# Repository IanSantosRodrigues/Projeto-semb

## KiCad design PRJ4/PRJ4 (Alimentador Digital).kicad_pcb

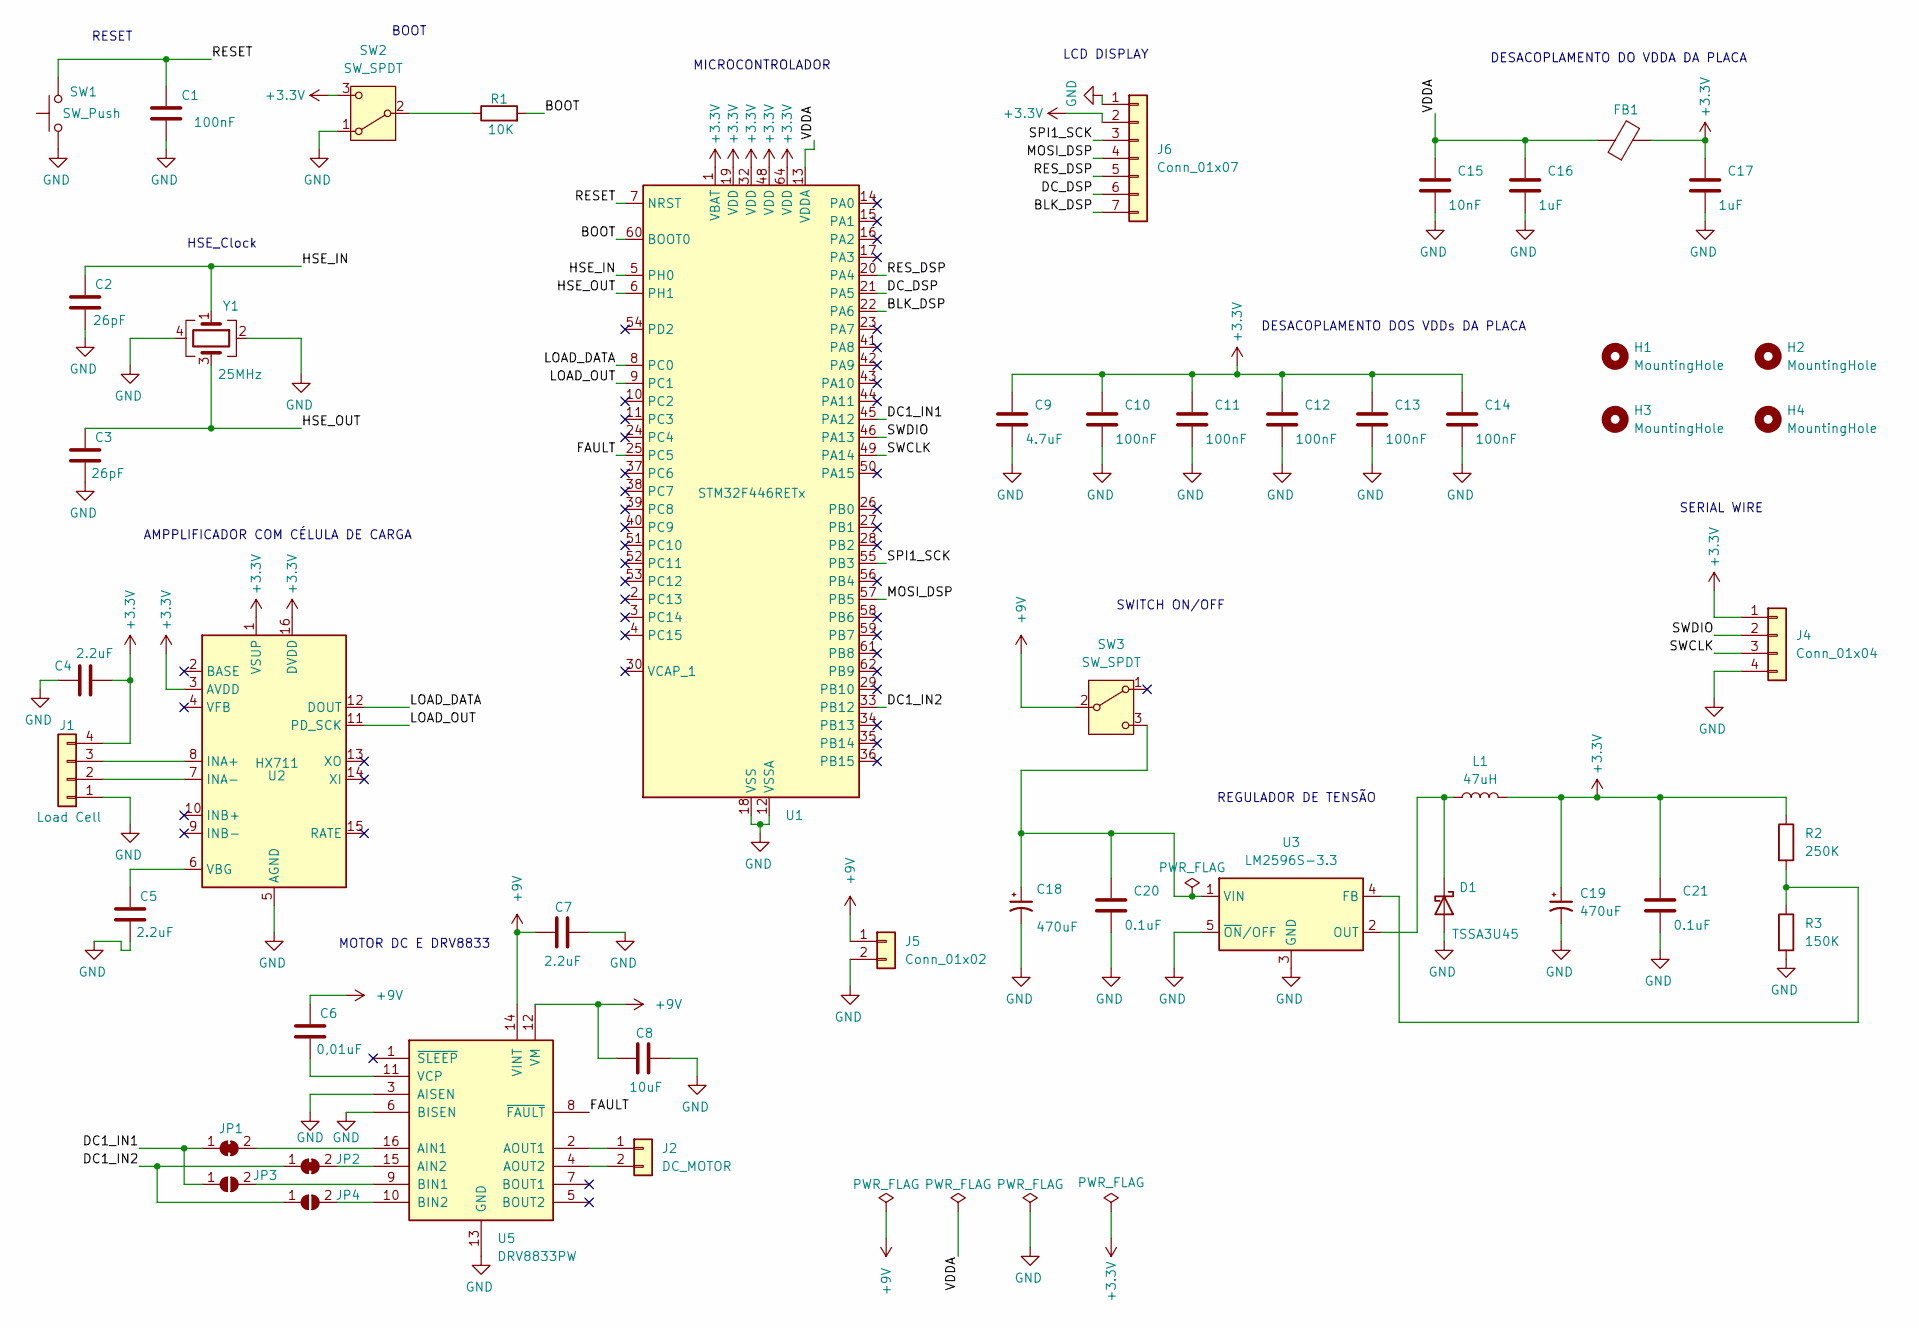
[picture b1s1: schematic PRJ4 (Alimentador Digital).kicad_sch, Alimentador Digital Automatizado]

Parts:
C1, C10, C11, C12, C13, C14: 100nF; C_0603_1608Metric
C2, C3: 26pF; C_0603_1608Metric
C4, C5, C7: 2.2uF; C_0603_1608Metric
C6: 0,01uF; C_0603_1608Metric
C8: 10uF; C_0603_1608Metric
C9: 4.7uF; C_0603_1608Metric
C15: 10nF; C_0603_1608Metric
C16, C17: 1uF; C_0603_1608Metric
C18, C19: 470uF; CP_Elec_10x12.5
C20, C21: 0.1uF; C_0603_1608Metric
D1: TSSA3U45; D_0603_1608Metric_Pad1.05x0.95mm_HandSolder
FB1: FerriteBead; L_0603_1608Metric_Pad1.05x0.95mm_HandSolder
H1, H2, H3, H4: MountingHole; MountingHole_3.2mm_M3
J1: Load Cell; PinHeader_1x04_P2.54mm_Vertical
J2: DC_MOTOR; PinHeader_1x02_P2.54mm_Vertical
J4: Conn_01x04; PinHeader_1x04_P2.54mm_Vertical
J5: Conn_01x02; PinHeader_1x02_P2.54mm_Vertical
J6: Conn_01x07; PinHeader_1x07_P2.54mm_Vertical
JP1, JP2: SolderJumper_2_Bridged; SolderJumper-2_P1.3mm_Bridged_RoundedPad1.0x1.5mm
JP3, JP4: SolderJumper_2_Open; SolderJumper-2_P1.3mm_Open_RoundedPad1.0x1.5mm
L1: 47uH; L_6.3x6.3_H3
R1: 10K; R_0603_1608Metric
R2: 250K; R_0805_2012Metric_Pad1.20x1.40mm_HandSolder
R3: 150K; R_0805_2012Metric_Pad1.20x1.40mm_HandSolder
SW1: SW_Push; SW_SPST_B3U-1000P-B
SW2, SW3: SW_SPDT; SW_SPDT_CK_JS102011SAQN
U1: STM32F446RETx; LQFP-64_10x10mm_P0.5mm
U2: HX711; SOP-16_3.9x9.9mm_P1.27mm
U3: LM2596S-3.3; TO-263-5_TabPin3
U5: DRV8833PW; TSSOP-16_4.4x5mm_P0.65mm
Y1: 25MHz; Crystal_SMD_SeikoEpson_FA238V-4Pin_3.2x2.5mm

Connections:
+3.3V: C4.2, C9.1, C10.1, C11.1, C12.1, C13.1, C14.1, C17.1, C19.1, C21.1, FB1.2, J1.4, J4.1, J6.2, L1.2, R2.1, SW2.3 (C), U1.1 (VBAT), U1.19 (VDD), U1.32 (VDD), U1.48 (VDD), U1.64 (VDD), U2.1 (VSUP), U2.3 (AVDD), U2.16 (DVDD)
+9V: C6.1, C7.1, C8.1, J5.1, SW3.2 (B), U5.12 (VM), U5.14 (VINT)
/BLK_DSP: J6.7, U1.22 (PA6)
/BOOT: R1.2, U1.60 (BOOT0)
/CLK__DSP: J6.3, U1.55 (PB3)
/DC1_IN1: JP1.1 (A), JP3.1 (A), U1.45 (PA12)
/DC1_IN2: JP2.1 (A), JP4.1 (A), U1.33 (PB12)
/DC_DSP: J6.6, U1.21 (PA5)
/FAULT: U1.25 (PC5), U5.8 (~FAULT)
/HSE_IN: C2.1, U1.5 (PH0), Y1.1
/HSE_OUT: C3.1, U1.6 (PH1), Y1.3
/LOAD_DATA: U1.8 (PC0), U2.12 (DOUT)
/LOAD_OUT: U1.9 (PC1), U2.11 (PD_SCK)
/MOSI_DSP: J6.4, U1.57 (PB5)
/RESET: C1.1, SW1.2, U1.7 (NRST)
/RES_DSP: J6.5, U1.20 (PA4)
/SWCLK: J4.3, U1.49 (PA14)
/SWDIO: J4.2, U1.46 (PA13)
/VDDA: C15.1, C16.1, FB1.1, U1.13 (VDDA)
GND: C1.2, C2.2, C3.2, C4.1, C5.2, C7.2, C8.2, C9.2, C10.2, C11.2, C12.2, C13.2, C14.2, C15.2, C16.2, C17.2, C18.2, C19.2, C20.2, C21.2, D1.2 (A), J1.1, J4.4, J5.2, J6.1, R3.2, SW1.1, SW2.1 (A), U1.12 (VSSA), U1.18 (VSS), U1.31 (VSS), U1.47 (VSS), U1.63 (VSS), U2.5 (AGND), U3.3 (GND), U3.5 (~ON/OFF), U5.3 (AISEN), U5.6 (BISEN), U5.13 (GND), Y1.2, Y1.4
unnamed: D1.1 (K), L1.1, U3.2 (OUT)
unnamed: J1.2, U2.7 (INA-)
unnamed: J1.3, U2.8 (INA+)
unnamed: J2.1, U5.2 (AOUT1)
unnamed: J2.2, U5.4 (AOUT2)
unnamed: JP1.2 (B), U5.16 (AIN1)
unnamed: JP2.2 (B), U5.15 (AIN2)
unnamed: JP3.2 (B), U5.9 (BIN1)
unnamed: JP4.2 (B), U5.10 (BIN2)
unnamed: R1.1, SW2.2 (B)
unnamed: C18.1, C20.1, SW3.3 (C), U3.1 (VIN)
unnamed: C5.1, U2.6 (VBG)
unnamed: R2.2, R3.1, U3.4 (FB)
unnamed: C6.2, U5.11 (VCP)

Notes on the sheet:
DESACOPLAMENTO DOS VDDs DA PLACA
MOTOR DC E DRV8833
RESET
DESACOPLAMENTO DO VDDA DA PLACA
REGULADOR DE TENSÃO
BOOT
HSE_Clock
LCD DISPLAY
MICROCONTROLADOR
SWITCH ON/OFF
SERIAL WIRE
AMPPLIFICADOR COM CÉLULA DE CARGA

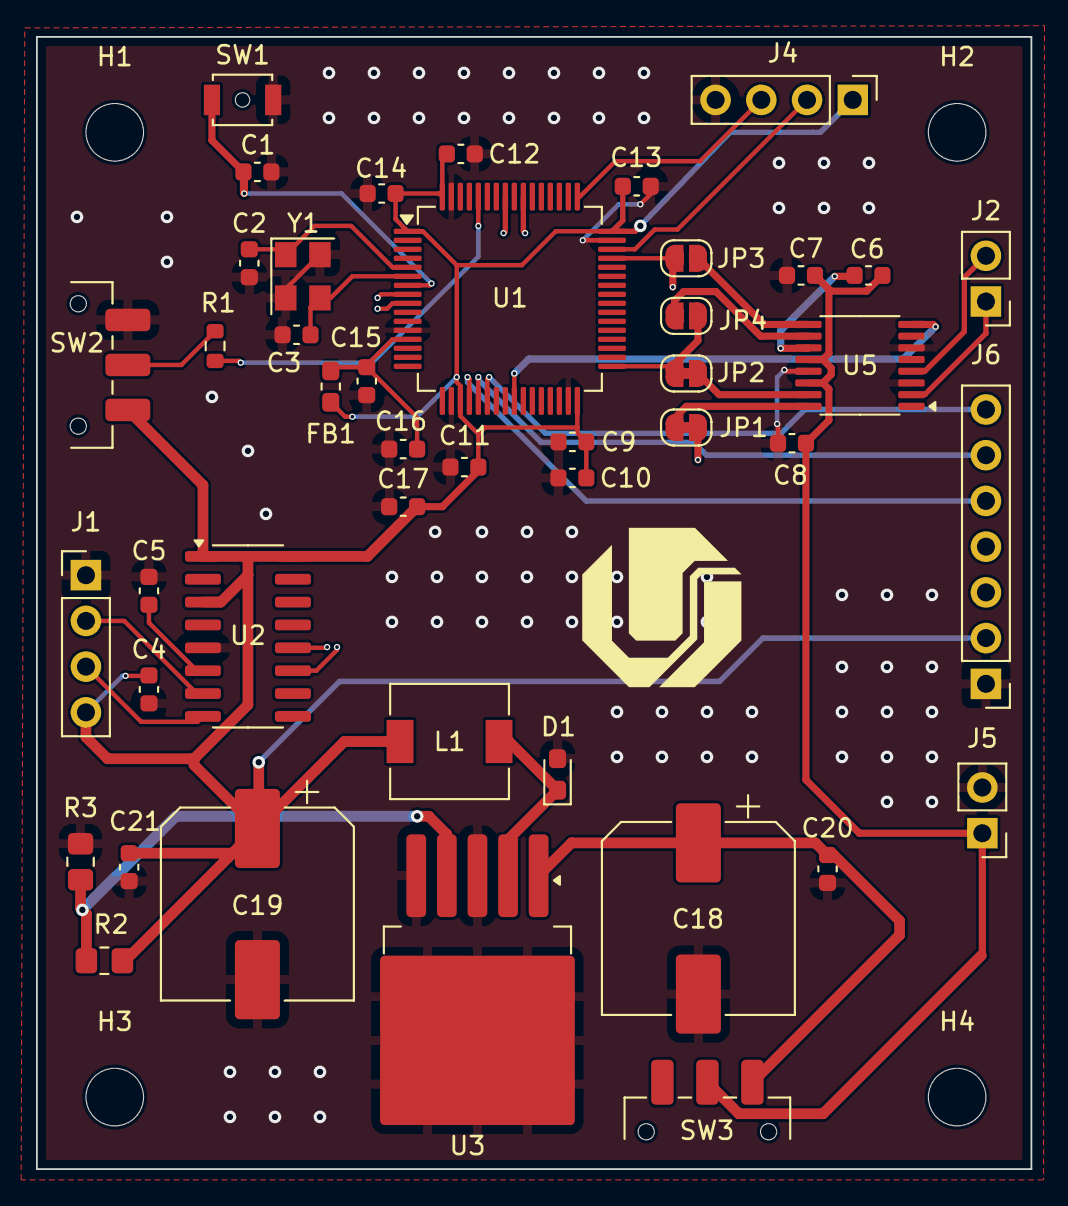
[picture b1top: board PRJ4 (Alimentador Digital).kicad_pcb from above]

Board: 4 copper layers, 55.2 x 62.9 mm, 48 parts (0 on the bottom side), 34 nets.

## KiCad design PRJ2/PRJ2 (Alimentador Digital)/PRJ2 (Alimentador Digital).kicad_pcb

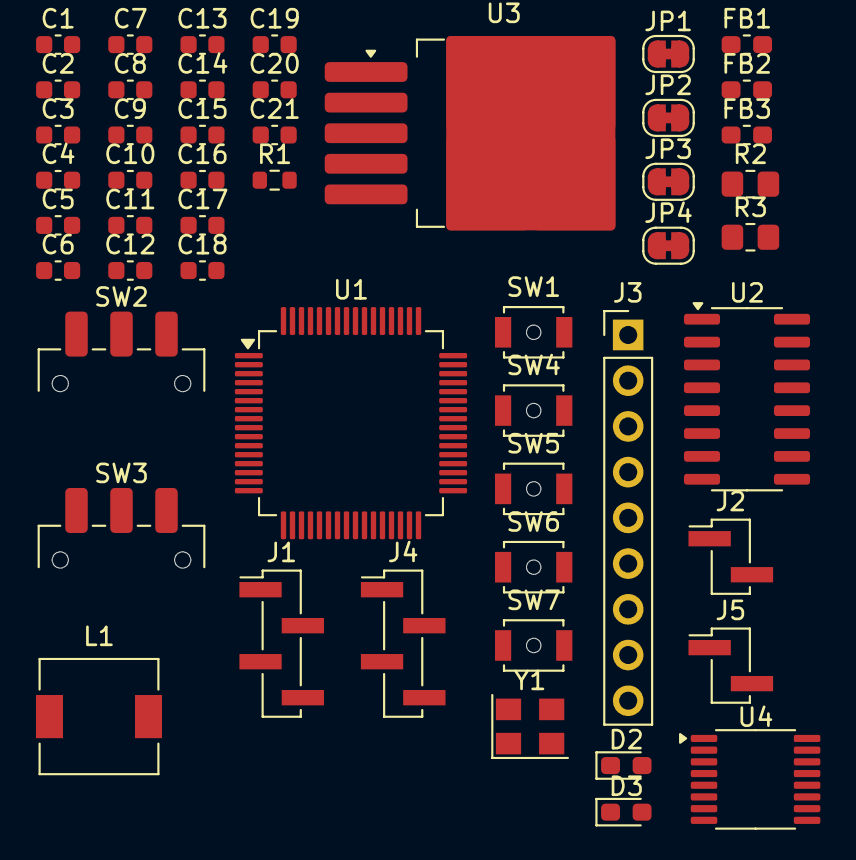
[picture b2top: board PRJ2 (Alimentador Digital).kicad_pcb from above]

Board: 2 copper layers, 51 parts (0 on the bottom side), 43 nets, no tracks yet.

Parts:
C1, C10, C11, C12, C13, C14: 100nF; C_0603_1608Metric
C2, C3: 26pF; C_0603_1608Metric
C4, C5, C7: 2.2uF; C_0603_1608Metric
C6: 0,01uF; C_0603_1608Metric
C8: 10uF; C_0603_1608Metric
C9: 4.7uF; C_0603_1608Metric
C15: 10nF; C_0603_1608Metric
C16, C17: 1uF; C_0603_1608Metric
C18, C19: 470uF; C_0603_1608Metric
C20, C21: 0.1uF; C_0603_1608Metric
D2: D_Zener; D_0603_1608Metric_Pad1.05x0.95mm_HandSolder
D3: TSSA3U45; D_0603_1608Metric_Pad1.05x0.95mm_HandSolder
FB1, FB2, FB3: FerriteBead; L_0603_1608Metric_Pad1.05x0.95mm_HandSolder
J1: Load Cell; PinHeader_1x04_P2.00mm_Vertical_SMD_Pin1Left
J2: DC_MOTOR; PinHeader_1x02_P2.00mm_Vertical_SMD_Pin1Left
J3: Conn_01x09; PinHeader_1x09_P2.54mm_Vertical
J4: Conn_01x04; PinHeader_1x04_P2.00mm_Vertical_SMD_Pin1Left
J5: Conn_01x02; PinHeader_1x02_P2.00mm_Vertical_SMD_Pin1Left
JP1, JP2, JP3, JP4: SolderJumper_2_Open; SolderJumper-2_P1.3mm_Bridged_RoundedPad1.0x1.5mm
L1: 47uH; L_6.3x6.3_H3
R1: 10K; R_0603_1608Metric
R2: 250K; R_0805_2012Metric_Pad1.20x1.40mm_HandSolder
R3: 150K; R_0805_2012Metric_Pad1.20x1.40mm_HandSolder
SW1: SW_Push; SW_SPST_B3U-1000P-B
SW2, SW3: SW_SPDT; SW_SPDT_CK_JS102011SAQN
SW4: BT4; SW_SPST_B3U-1000P-B
SW5: BT3; SW_SPST_B3U-1000P-B
SW6: BT2; SW_SPST_B3U-1000P-B
SW7: BT1; SW_SPST_B3U-1000P-B
U1: STM32F446RETx; LQFP-64_10x10mm_P0.5mm
U2: HX711; SOP-16_3.9x9.9mm_P1.27mm
U3: LM2596S-3.3; TO-263-5_TabPin3
U4: DRV8833PW; TSSOP-16_4.4x5mm_P0.65mm
Y1: 25MHz; Crystal_SMD_SeikoEpson_FA238V-4Pin_3.2x2.5mm

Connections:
+3.3V: C4.2, C9.1, C10.1, C11.1, C12.1, C13.1, C14.1, C17.1, FB1.2, FB2.2, FB3.2, J1.4, J4.1, SW2.3 (C), SW4.2, SW5.2, SW6.2, SW7.2, U1.1 (VBAT), U1.19 (VDD), U1.32 (VDD), U1.48 (VDD), U1.64 (VDD), U2.1 (VSUP), U2.3 (AVDD), U2.16 (DVDD)
+9V: C6.1, C7.1, C8.1, C18.1, C20.1, J5.1, U3.1 (VIN), U4.12 (VM), U4.14 (VINT)
/BOOT: R1.2, U1.60 (BOOT0)
/BT1: SW7.1, U1.26 (PB0)
/BT2: SW6.1, U1.27 (PB1)
/BT3: SW5.1, U1.28 (PB2)
/BT4: SW4.1, U1.55 (PB3)
/DC1_IN1: JP1.1 (A), JP3.1 (A), U1.11 (PC3)
/DC1_IN2: JP2.1 (A), JP4.1 (A), U1.24 (PC4)
/DISPL_CS: J3.5, U1.33 (PB12)
/DISPL_DC: J3.7, U1.35 (PB14)
/DISPL_LED: J3.9, U1.38 (PC7)
/DISPL_MOSI: J3.4, U1.23 (PA7)
/DISPL_RST: J3.8, U1.36 (PB15)
/DISPL_SCK: J3.2, U1.21 (PA5)
/FAULT: U1.25 (PC5), U4.8 (~FAULT)
/HSE_IN: C2.1, U1.5 (PH0), Y1.1
/HSE_OUT: C3.1, U1.6 (PH1), Y1.3
/LOAD_DATA: U1.8 (PC0), U2.12 (DOUT)
/LOAD_OUT: U1.9 (PC1), U2.11 (PD_SCK)
/RESET: C1.1, SW1.2, U1.7 (NRST)
/R_OUT: C19.1, C21.1, L1.2, R2.1, SW3.2 (B)
/SWCLK: J4.3, U1.49 (PA14)
/SWDIO: J4.2, U1.46 (PA13)
/TOUCH_CS: J3.6, U1.34 (PB13)
/TOUCH_MOSI: J3.3, U1.22 (PA6)
/TOUNH_INT: J3.1, U1.20 (PA4)
/VDDA: C15.1, C16.1, FB1.1, U1.13 (VDDA)
GND: C1.2, C2.2, C3.2, C4.1, C5.2, C7.2, C8.2, C9.2, C10.2, C11.2, C12.2, C13.2, C14.2, C15.2, C16.2, C17.2, C18.2, C19.2, C20.2, C21.2, D2.2 (A), D3.2 (A), J1.1, J4.4, J5.2, R3.2, SW1.1, SW2.1 (A), U1.12 (VSSA), U1.18 (VSS), U1.31 (VSS), U1.47 (VSS), U1.63 (VSS), U2.5 (AGND), U3.3 (GND), U3.5 (~ON/OFF), U4.3 (AISEN), U4.6 (BISEN), U4.13 (GND), Y1.2, Y1.4
unnamed: D2.1 (K), R1.1, SW2.2 (B)
unnamed: D3.1 (K), L1.1, U3.2 (OUT)
unnamed: J1.2, U2.7 (INA-)
unnamed: J1.3, U2.8 (INA+)
unnamed: J2.1, U4.2 (AOUT1)
unnamed: J2.2, U4.4 (AOUT2)
unnamed: JP1.2 (B), U4.16 (AIN1)
unnamed: JP2.2 (B), U4.15 (AIN2)
unnamed: JP3.2 (B), U4.9 (BIN1)
unnamed: JP4.2 (B), U4.10 (BIN2)
unnamed: FB2.1, FB3.1, SW3.1 (A)
unnamed: C5.1, U2.6 (VBG)
unnamed: R2.2, R3.1, U3.4 (FB)
unnamed: C6.2, U4.11 (VCP)

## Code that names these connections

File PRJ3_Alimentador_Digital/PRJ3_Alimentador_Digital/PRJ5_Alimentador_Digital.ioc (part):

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Mcu.Name=STM32F446R(C-E)Tx
Mcu.Package=LQFP64
Mcu.UserName=STM32F446RETx
PA12.GPIOParameters=GPIO_Label
PA12.GPIO_Label=DC1_IN1
PA12.Signal=GPIO_Input
PA13.GPIOParameters=GPIO_Label
PA13.GPIO_Label=SWDIO
PA13.Mode=Serial_Wire
PA13.Signal=SYS_JTMS-SWDIO
PA14.GPIOParameters=GPIO_Label
PA14.GPIO_Label=SWCLK
PA14.Mode=Serial_Wire
PA14.Signal=SYS_JTCK-SWCLK
PA4.GPIOParameters=GPIO_Label
PA4.GPIO_Label=RESET_DSP
PA4.Signal=GPIO_Output
PA5.GPIOParameters=GPIO_Label
PA5.GPIO_Label=DC_DSP
PA5.Signal=GPIO_Output
PA6.GPIOParameters=GPIO_Label
PA6.GPIO_Label=BLK_DSP
PA6.Signal=GPIO_Output
PB12.GPIOParameters=GPIO_Label
PB12.GPIO_Label=DC1_IN2
PB12.Signal=GPIO_Output
PB3.GPIOParameters=GPIO_Label
PB3.GPIO_Label=SCL_DSP
PB3.Mode=TX_Only_Simplex_Unidirect_Master
PB3.Signal=SPI1_SCK
PB5.GPIOParameters=GPIO_Label
PB5.GPIO_Label=SDA_DSP
PB5.Mode=TX_Only_Simplex_Unidirect_Master
PB5.Signal=SPI1_MOSI
PC0.GPIOParameters=GPIO_Label
PC0.GPIO_Label=LOAD_DATA
PC0.Signal=GPIO_Input
PC1.GPIOParameters=GPIO_Label
PC1.GPIO_Label=LOAD_CLK
PC1.Signal=GPIO_Input
PC5.GPIOParameters=GPIO_Label
PC5.GPIO_Label=FAULT
PC5.Signal=GPIO_Input
PH0-OSC_IN.GPIOParameters=GPIO_Label
PH0-OSC_IN.GPIO_Label=HSE_IN
PH0-OSC_IN.Mode=HSE-External-Oscillator
PH0-OSC_IN.Signal=RCC_OSC_IN
PH1-OSC_OUT.GPIOParameters=GPIO_Label
PH1-OSC_OUT.GPIO_Label=HSE_OUT
PH1-OSC_OUT.Mode=HSE-External-Oscillator
PH1-OSC_OUT.Signal=RCC_OSC_OUT
RCC.HSE_VALUE=25000000
RCC.SYSCLKFreq_VALUE=25000000
RCC.SYSCLKSource=RCC_SYSCLKSOURCE_HSE
board=custom

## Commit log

2025-04-23 add text
2025-04-23 criar app
2025-04-23 inserido algumas funções
2025-04-23 atualizado funções
2025-04-24 criação das primeiras funções
2025-04-24 atualizado app.c
2025-04-24 simplificado headers
2025-04-24 implementado funções do display
2025-04-24 separado as funções do display e estruturado melhor
2025-04-24 att da pcb
2025-04-24 att da pcb v2
2025-04-24 criado pasta Inc e Src dentro do código de autoria
2025-04-25 backups
2025-04-30 atualizou pinagem do display
2025-04-30 nomes do pinos
2025-04-30 mudei os pinos
2025-04-30 pasta
2025-04-30 nada
2025-04-30 arquivo deletado
2025-04-30 Alterações no repositório
2025-05-02 alguma alteração que não sei
2025-05-02 display atualizado e código compilando com sucesso
2025-05-02 Utima alteração para entregar o projeto
2025-05-02 finalizado
2025-05-02 zip final
2025-05-02 projeto 5 zipado
2025-05-02 exportado da forma correta
